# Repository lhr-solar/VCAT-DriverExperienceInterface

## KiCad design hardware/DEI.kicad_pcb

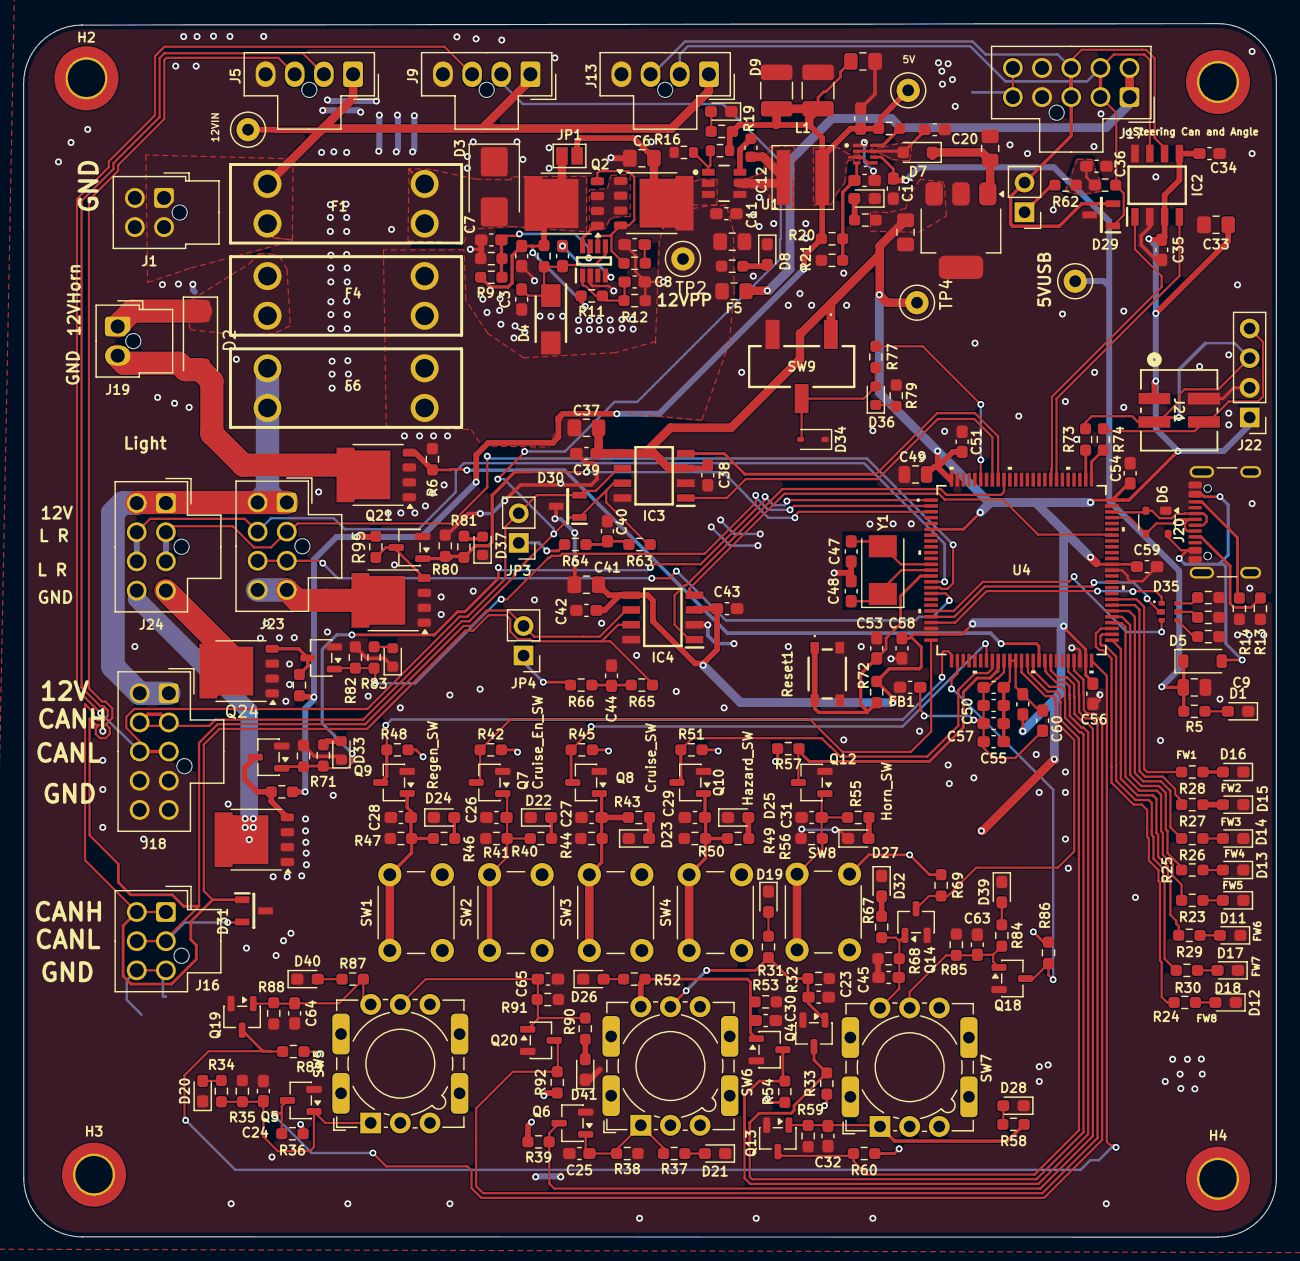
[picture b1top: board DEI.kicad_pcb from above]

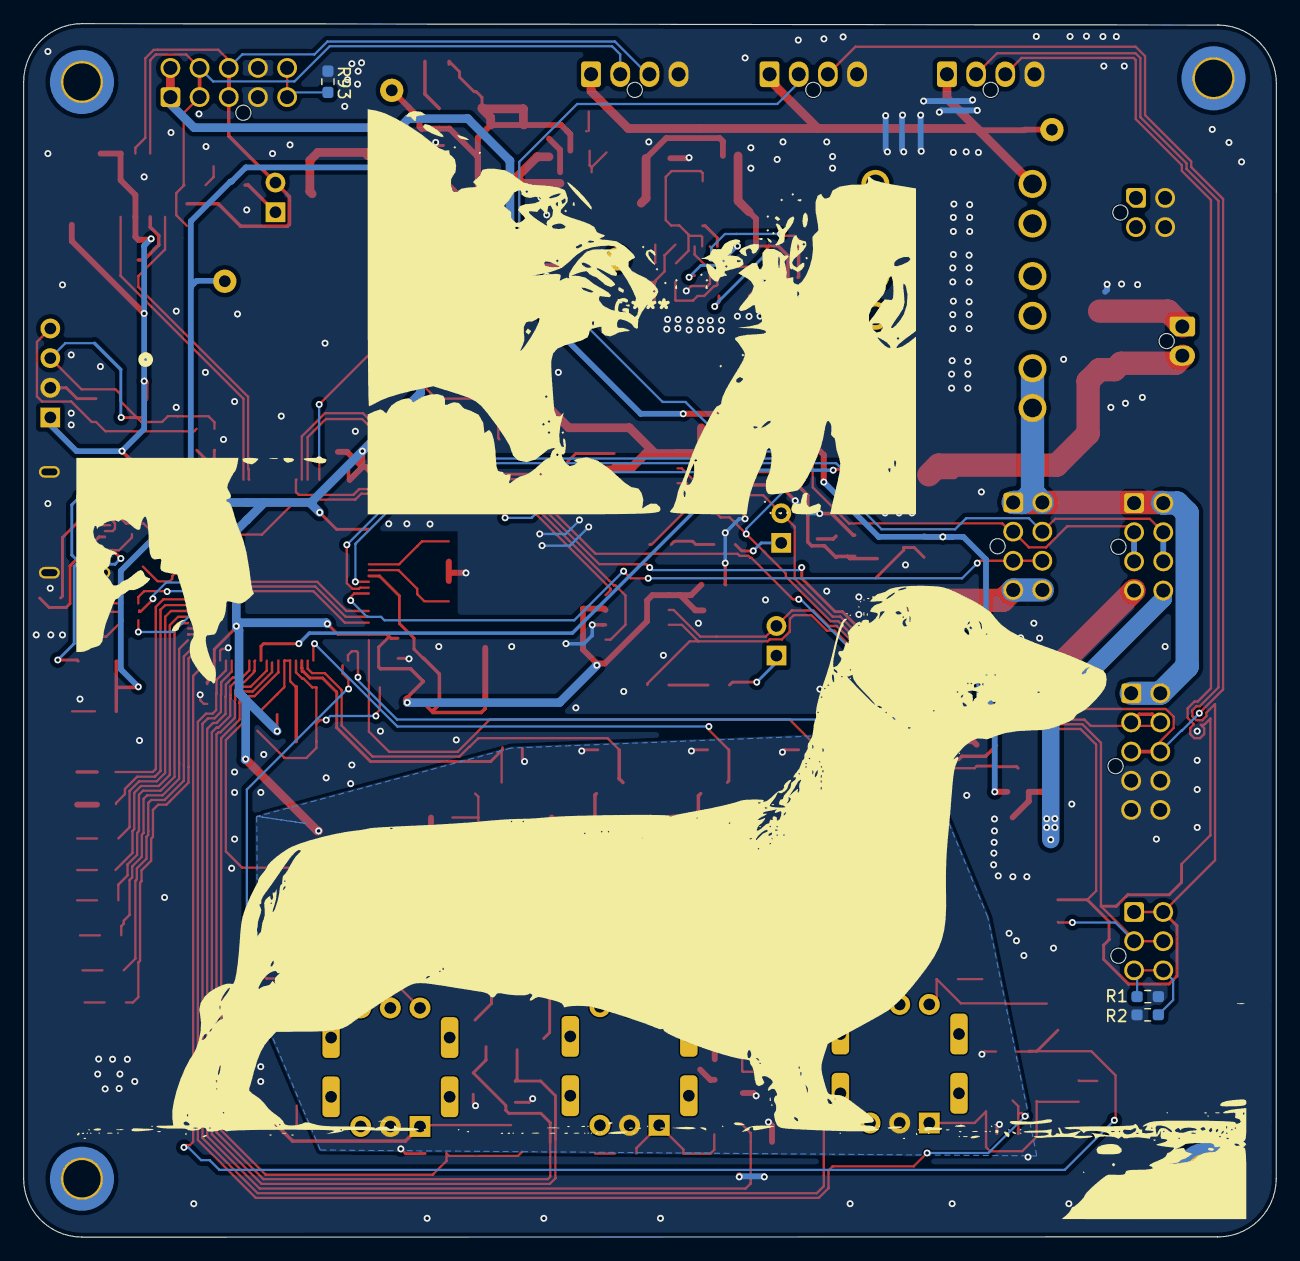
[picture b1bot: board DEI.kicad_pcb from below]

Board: 2 copper layers, 107.4 x 104.0 mm, 270 parts (3 on the bottom side), 146 nets.

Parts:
5V_USB1: TestPoint; TestPoint_Loop_D1.80mm_Drill1.0mm_Beaded
C2, C7, C8, C16, C17, C18, C19, C34, C35, C36, C38, C39, C40, C42, C43, C44, C50, C51, C52, C53, C54, C56, C58, C59, C60: 0.1u; C_0603_1608Metric_Pad1.08x0.95mm_HandSolder
C3, C55, C57: 1u; C_0603_1608Metric_Pad1.08x0.95mm_HandSolder
C4: 220n; C_0603_1608Metric_Pad1.08x0.95mm_HandSolder
C5: 10n; C_0603_1608Metric_Pad1.08x0.95mm_HandSolder
C6, C20, C21, C33, C37, C41: 10u; C_0805_2012Metric_Pad1.18x1.45mm_HandSolder
C9, C49: 10u; C_0805_2012Metric
C10: 4.7u; C_0805_2012Metric_Pad1.18x1.45mm_HandSolder
C11, C23, C24, C25, C26, C27, C28, C29, C30, C31, C32, C45, C63, C64, C65: 100n; C_0603_1608Metric_Pad1.08x0.95mm_HandSolder
C12: 100n; C_0603_1608Metric
C13, C14: 22u; C_1210_3225Metric_Pad1.33x2.70mm_HandSolder
C15: 3.3u; C_0805_2012Metric_Pad1.18x1.45mm_HandSolder
C47, C48: 26p; C_0603_1608Metric_Pad1.08x0.95mm_HandSolder
D1, D9, D10, D11, D12, D13, D14, D15, D17: Status LED; LED_0603_1608Metric_Pad1.05x0.95mm_HandSolder
D2: D; D_SlimSMA_DO-221AC_Pad1.90x1.60mm_HandSolder
D3: SMBJ15CA; D_SMB
D4: SMAF4758A; SODFL5026X125N
D5: D_Schottky; D_SOD-123
D6: SP0503BAHT; SOT-143
D7: SBA130CH-AU_R1_000A1; D_SOD-323_HandSoldering
D8: 12V Power; LED_0603_1608Metric_Pad1.05x0.95mm_HandSolder
D16: Firmware- Green LEDs; LED_0603_1608Metric_Pad1.05x0.95mm_HandSolder
D18: Firmware green led; LED_0603_1608Metric_Pad1.05x0.95mm_HandSolder
D19, D20, D21, D22, D23, D24, D25, D26, D27, D28, D32, D39, D40, D41: Blue Status; LED_0603_1608Metric_Pad1.05x0.95mm_HandSolder
D29, D30, D31: CDSOT23-T24CAN
D33, D36, D37, D38: LED; LED_0603_1608Metric
D34: TVS; D_SOD-323
D35: RGB_LED
F1: Fuse; Fuse-3557-2
F4: .5A; Fuse-3557-2
F5: 200mA; Fuse_0805_2012Metric_Pad1.15x1.40mm_HandSolder
F6: TBD; Fuse-3557-2
FB1, FB2: FerriteBead; C_0603_1608Metric_Pad1.08x0.95mm_HandSolder
H1, H2, H3, H4: m3; MountingHole_3.2mm_M3_ISO14580_Pad_TopBottom
IC1: LM74502DDFR
IC2, IC3, IC4: TCAN3413DR
J1: Power Input; Molex_Nano-Fit_105310-xx04_2x02_P2.50mm_Vertical
J5: Car_Can_Debug; Molex_Nano-Fit_105309-xx04_1x04_P2.50mm_Vertical
J9: Lighting_Can_Debug; Molex_Nano-Fit_105309-xx04_1x04_P2.50mm_Vertical
J13: Steering_Can_Debug; Molex_Nano-Fit_105309-xx04_1x04_P2.50mm_Vertical
J16: CAN_NANO_02x03; Molex_Nano-Fit_105310-xx06_2x03_P2.50mm_Vertical
J17: Steering Can; Molex_Nano-Fit_105310-xx10_2x05_P2.50mm_Vertical
J18: LightingCan; Molex_Nano-Fit_105310-xx10_2x05_P2.50mm_Vertical
J19: Horn; Molex_Nano-Fit_105309-xx02_1x02_P2.50mm_Vertical
J20: USB_C_Receptacle_USB2.0_16P; USB_C_Receptacle_GCT_USB4105-xx-A_16P_TopMnt_Horizontal
J21: SWD_Header; SWD_Conn
J22: SWD; PinHeader_1x04_P2.54mm_Vertical
J23: HeadLights; Molex_Nano-Fit_105310-xx08_2x04_P2.50mm_Vertical
J24: Light Strip; Molex_Nano-Fit_105310-xx08_2x04_P2.50mm_Vertical
JP1: SolderJumper_2_Open; SolderJumper-2_P1.3mm_Open_Pad1.0x1.5mm
JP2, JP3, JP4: TRM; PinHeader_1x02_P2.54mm_Vertical
L1: 8.2u; XAL5050822MEC
Q2, Q3, Q21, Q22, Q23, Q24: PSMN012-100YS; LFPAK56
Q4, Q5, Q6, Q7, Q8, Q9, Q10, Q11, Q12, Q13, Q14, Q15, Q16, Q17, Q18, Q19, Q20: Q_NMOS_GSD; SOT-23-3
R1, R2, R93: 0; R_0603_1608Metric_Pad0.98x0.95mm_HandSolder
R5, R19: 2.2k; R_0603_1608Metric_Pad0.98x0.95mm_HandSolder
R6, R7, R17, R33, R36, R39, R42, R45, R48, R51, R54, R57, R60, R69, R70, R72, R77, R80, R82, R86, R89, R92, R94, R95, R96: 10k; R_0603_1608Metric_Pad0.98x0.95mm_HandSolder
R8: 33; R_0603_1608Metric_Pad0.98x0.95mm_HandSolder
R9, R11, R32, R35, R38, R41, R44, R47, R50, R53, R56, R59, R68, R85, R88, R91: 100k; R_0603_1608Metric_Pad0.98x0.95mm_HandSolder
R10: 7.32k; R_0603_1608Metric_Pad0.98x0.95mm_HandSolder
R12: 15.8k; R_0603_1608Metric_Pad0.98x0.95mm_HandSolder
R13, R14, R18: 5.1k; R_0603_1608Metric_Pad0.98x0.95mm_HandSolder
R15: 100k; R_0603_1608Metric
R16: 19.1k; R_0603_1608Metric
R20: 16k; R_0603_1608Metric_Pad0.98x0.95mm_HandSolder
R21: 4.7k; R_0603_1608Metric_Pad0.98x0.95mm_HandSolder
R22, R23, R24, R25, R26, R27, R28, R29, R30, R31, R34, R37, R40, R43, R46, R49, R52, R55, R58, R67, R71, R75, R76, R78, R79, R81, R83, R84, R87, R90: 1k; R_0603_1608Metric_Pad0.98x0.95mm_HandSolder
R61, R62, R63, R64, R65, R66: 60; R_0603_1608Metric_Pad0.98x0.95mm_HandSolder
R73, R74: 22; R_0603_1608Metric_Pad0.98x0.95mm_HandSolder
Reset1: Reset; TL3365AF180QG
SW1: Regen; SW_PUSH_6mm
SW2: Cruise Enable; SW_PUSH_6mm
SW3: Cruise; SW_PUSH_6mm
SW4: Hazard; SW_PUSH_6mm
SW5, SW6, SW7: SW_SP3T_NR01103; SW_NKK_NR01
SW8: Horn; SW_PUSH_6mm
SW9: SW_SPDT; BootSW
TP1: 12V_In; TestPoint_Loop_D1.80mm_Drill1.0mm_Beaded
TP2: 12V_PP; TestPoint_Loop_D1.80mm_Drill1.0mm_Beaded
TP3: 5VBuck; TestPoint_Loop_D1.80mm_Drill1.0mm_Beaded
TP4: 3.3V_LDO; TestPoint_Loop_D1.80mm_Drill1.0mm_Beaded
U1: LMR51635XDDCR; DDC0006A-MFG
U2: TPS2117DRLR
U3: MCP1826S; SOT-223-3_TabPin2
U4: STM32G473VETx; 100PinMCU
Y1: Crystal; Crystal_SMD_Abracon_ABM3-2Pin_5.0x3.2mm

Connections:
+3.3V: C21.2, C33.1, C34.1, C35.1, C37.1, C38.1, C39.1, C41.1, C42.1, C43.1, C49.1, C51.1, C54.1, C56.1, C58.1, C59.1, FB2.1, IC2.3 (VCC), IC2.5 (SHDNV_IO), IC3.3 (VCC), IC3.5 (SHDNV_IO), IC4.3 (VCC), IC4.5 (SHDNV_IO), J21.1, J22.1, R22.1, R33.1, R36.1, R39.1, R42.1, R45.1, R48.1, R51.1, R54.1, R57.1, R60.1, R69.1, R72.2, R86.1, R89.1, R92.1, SW1.2, SW2.2, SW3.2, SW4.2, SW5.C (Common), SW6.C (Common), SW7.C (Common), SW8.2, SW9.1 (A), TP4.1 (1_1), U3.3 (VO), U4.6 (VBAT), U4.24 (VDD), U4.49 (VDD), U4.64 (VDD), U4.75 (VDD), U4.100 (VDD)
+12V: F1.1, J1.1, J1.2, J5.1 (12V), J9.1 (12V), J13.1 (12V), TP1.1 (1_1)
/5V: C13.1, C14.1, C15.1, C16.1, L1.2, R15.1, R17.1, R19.1, R20.1, R94.1, R95.1, R96.1, TP3.1 (1_1), U2.3 (VIN1), U2.5 (MODE)
/12V_Horn: D2.1 (K), F4.2, J19.1
/12V_Light: F6.2, J18.1 (12V), J18.10 (12V), J23.1, J23.8, J24.1, J24.8
/12V_Steering_Angle: F5.2, J17.1 (12V), J17.10 (12V)
/CarCan_H: D31.1 (CAN_H), IC4.7 (CANH), J5.2 (CAN_H), J16.1 (CAN_H), J16.6 (CAN_H), R65.1
/CarCan_L: D31.2 (CAN_L), IC4.6 (CANL), J5.3 (CAN_L), J16.2 (CAN_L), J16.5 (CAN_L), JP4.2 (B)
/Head: J23.3, J23.6, U4.17 (PC2)
/Head_GND: J23.4, J23.5, Q23.5
/Head_On: Q16.1 (G), R80.1, R81.1, U4.3 (PE4)
/Horn: D2.2 (A), J19.2, Q21.5
/Horn_In: Q21.4, R6.1, U4.41 (PE10)
/Left_GND: J24.5, Q22.5
/Left_On: Q15.1 (G), R70.1, R71.1, U4.1 (PE2)
/Left_Turn: J23.7, J24.6, J24.7, U4.15 (PC0)
/LightingCan_H: D30.1 (CAN_H), IC3.7 (CANH), J9.2 (CAN_H), J18.2 (CAN_H), J18.9 (CAN_H), R63.1
/LightingCan_L: D30.2 (CAN_L), IC3.6 (CANL), J9.3 (CAN_L), J18.3 (CAN_L), J18.8 (CAN_L), JP3.2 (B)
/MCU/100PinMCU/BOOT0: R77.1, U4.95 (PB8-BOOT0)
/MCU/100PinMCU/GNDA: C50.2, C52.2, C55.2, C57.2, C60.2, FB1.1, U4.35 (VSSA)
/MCU/100PinMCU/NRST: C53.1, R72.1, Reset1.1, U4.14 (PG10-NRST)
/MCU/100PinMCU/PA0: D35.5, U4.20 (PA0-GPIO_BLUE)
/MCU/100PinMCU/PA1: D35.3, U4.21 (PA1-GPIO_RED)
/MCU/100PinMCU/PA2: D35.1, U4.22 (PA2-GPIO_GREEN)
/MCU/100PinMCU/PB12: R29.2, U4.51 (PB12)
/MCU/100PinMCU/PB13: R30.2, U4.52 (PB13)
/MCU/100PinMCU/PB14: R24.2, U4.53 (PB14)
/MCU/100PinMCU/PB15: R23.2, U4.54 (PB15)
/MCU/100PinMCU/PD8: R25.2, U4.55 (PD8)
/MCU/100PinMCU/PD9: R26.2, U4.56 (PD9)
/MCU/100PinMCU/PD10: R27.2, U4.57 (PD10)
/MCU/100PinMCU/PD11: R28.2, U4.58 (PD11)
/MCU/100PinMCU/SWCLK: R73.1, U4.77 (PA14)
/MCU/100PinMCU/SWDIO: R74.1, U4.76 (PA13)
/MCU/100PinMCU/VDDA: C50.1, C52.1, C55.1, C57.1, C60.1, FB2.2, U4.36 (VREF+), U4.37 (VDDA)
/MCU/CARCAN_RX: IC4.4 (RXD), U4.69 (PA8)
/MCU/CARCAN_TX: IC4.1 (TXD), U4.91 (PB4)
/MCU/Cruise_Out: Q8.3 (D), R45.2, U4.32 (PB0)
/MCU/Cruise_enable_out: Q7.3 (D), R42.2, U4.25 (PA3)
/MCU/GEAR_F_IN: C32.1, Q13.1 (G), R58.1, R59.1, SW7.1
/MCU/Gear_F_Out: Q13.3 (D), R60.2, U4.39 (PE8)
/MCU/Gear_N: C45.1, Q14.1 (G), R67.1, R68.1, SW7.2
/MCU/Gear_N_Out: Q14.3 (D), R69.2, U4.38 (PE7)
/MCU/Gear_out: Q18.3 (D), R86.2, U4.27 (PA5)
/MCU/Hazard_Out: Q10.3 (D), R51.2, U4.33 (PB1)
/MCU/Horn_Out: Q12.3 (D), R57.2, U4.34 (PB2)
/MCU/IGN_ARR_IN: C30.1, Q11.1 (G), R52.1, R53.1, SW6.2
/MCU/IGN_ARR_O: Q11.3 (D), R54.2, U4.42 (PE11)
/MCU/IGN_MTR_IN: C25.1, Q6.1 (G), R37.1, R38.1, SW6.1
/MCU/IGN_O: Q6.3 (D), R39.2, U4.43 (PE12)
/MCU/IGN_O_Out: Q4.3 (D), R33.2, U4.40 (PE9)
/MCU/IGN_Off: C23.1, Q4.1 (G), R31.1, R32.1, SW6.3
/MCU/LIGHTCAN_RX: IC3.4 (RXD), U4.92 (PB5)
/MCU/LIGHTCAN_TX: IC3.1 (TXD), U4.93 (PB6)
/MCU/NMOS4/Gate: C26.1, Q7.1 (G), R40.1, R41.1, SW2.1
/MCU/NMOS5/Gate: C27.1, Q8.1 (G), R43.1, R44.1, SW3.1
/MCU/NMOS6/Gate: C28.1, Q9.1 (G), R46.1, R47.1, SW1.1
/MCU/NMOS7/Gate: C29.1, Q10.1 (G), R49.1, R50.1, SW4.1
/MCU/NMOS11/Gate: C31.1, Q12.1 (G), R55.1, R56.1, SW8.1
/MCU/NMOS16/Gate: C63.1, Q18.1 (G), R84.1, R85.1, SW7.3
/MCU/Regen_Out: Q9.3 (D), R48.2, U4.26 (PA4)
/MCU/STEERCAN_RX: IC2.4 (RXD), U4.82 (PD0)
/MCU/STEERCAN_TX: IC2.1 (TXD), U4.83 (PD1)
/MCU/Steering_M: C64.1, Q19.1 (G), R87.1, R88.1, SW5.2
/MCU/Turn_L_IN: C24.1, Q5.1 (G), R34.1, R35.1, SW5.1
/MCU/Turn_L_Out: Q5.3 (D), R36.2, U4.47 (PB10)
/MCU/Turn_Middle: Q19.3 (D), R89.2, U4.50 (PB11)
/MCU/Turn_R_IN: C65.1, Q20.1 (G), R90.1, R91.1, SW5.3
/MCU/Turn_R_out: Q20.3 (D), R92.2, U4.46 (PE15)
/Power/12VBuck/CB: C12.1, U1.6 (CB)
/Power/12VBuck/FB: R15.2, R16.1, U1.1 (FB)
/Power/12VBuck/SW: C12.2, L1.1, U1.5 (SW)
/Power/12VBuck/V_in_12V: C6.1, C10.1, C11.1, F4.1, F5.1, F6.1, JP1.2 (B), Q3.5, R18.1, TP2.1 (1_1), U1.2 (EN), U1.3 (VIN)
/Power/LDO/Vin: C19.1, D7.2 (A), U2.2 (VOUT), U2.7 (VOUT__1)
/Power/PowerProtection/EN/UVLO: C8.1, IC1.1 (EN/UVLO), R11.2, R12.2
/Power/PowerProtection/OV: C7.1, IC1.7 (OV), R9.2, R10.1
/Power/PowerProtection/Vin: C2.1, D3.2 (A2), F1.2, JP1.1 (A), Q2.5, R7.2, R9.1, R11.1
/Power/PowerProtection/gate: IC1.6 (GATE), Q2.4, Q3.4, R8.2
/Power/PowerProtection/source: IC1.8 (SRC), Q2.1, Q2.2, Q2.3, Q3.1, Q3.2, Q3.3
/Power/Power_Mux/PR1: C18.1, R20.2, R21.1, U2.4 (PR1)
/Right_GND: J24.4, Q24.5
/Right_On: Q17.1 (G), R82.1, R83.1, U4.2 (PE3)
/Right_Turn: J23.2, J24.2, J24.3, U4.16 (PC1)
/SteeringCan_H: D29.1 (CAN_H), IC2.7 (CANH), J13.2 (CAN_H), J17.2 (CAN_H), J17.9 (CAN_H), R61.1
/SteeringCan_L: D29.2 (CAN_L), IC2.6 (CANL), J13.3 (CAN_L), J17.3 (CAN_L), J17.8 (CAN_L), JP2.2 (B)
/USB5V: 5V_USB1.1 (1_1), C9.2, C17.1, D5.1 (K), R5.1, U2.6 (VIN2)
/USB-C_Connector/CC1: J20.A5 (CC1), R13.2
/USB-C_Connector/CC2: J20.B5 (CC2), R14.2
/USB-C_Connector/VBUS_IN: D5.2 (A), D6.4 (K), J20.A4 (VBUS), J20.A9 (VBUS), J20.B4 (VBUS), J20.B9 (VBUS)
/USB_D+: D6.2 (K), J20.A6 (D+), J20.B6 (D+), U4.73 (PA12)
/USB_D-: D6.3 (K), J20.A7 (D-), J20.B7 (D-), U4.72 (PA11)
GND: C2.2, C3.1, C5.2, C6.2, C7.2, C8.2, C9.1, C10.2, C11.2, C13.2, C14.2, C15.2, C16.2, C17.2, C18.2, C19.2, C20.1, C21.1, C23.2, C24.2, C25.2, C26.2, C27.2, C28.2, C29.2, C30.2, C31.2, C32.2, C33.2, C34.2, C35.2, C36.1, C37.2, C38.2, C39.2, C40.1, C41.2, C42.2, C43.2, C44.1, C45.2, C47.1, C48.1, C49.2, C51.2, C53.2, C54.2, C56.2, C58.2, C59.2, C63.2, C64.2, C65.2, D1.1 (K), D3.1 (A1), D4.2 (A), D6.1 (A), D8.1 (K), D9.1 (K), D10.1 (K), D11.1 (K), D12.1 (K), D13.1 (K), D14.1 (K), D15.1 (K), D16.1 (K), D17.1 (K), D18.1 (K), D19.1 (K), D20.1 (K), D21.1 (K), D22.1 (K), D23.1 (K), D24.1 (K), D25.1 (K), D26.1 (K), D27.1 (K), D28.1 (K), D29.3 (GND), D30.3 (GND), D31.3 (GND), D32.1 (K), D33.1 (K), D34.1 (A1), D37.1 (K), D38.1 (K), D39.1 (K), D40.1 (K), D41.1 (K), FB1.2, IC1.2 (GND), IC2.2 (GND), IC2.8 (STB), IC3.2 (GND), IC3.8 (STB), IC4.2 (GND), IC4.8 (STB), J1.3, J1.4, J5.4 (GND), J9.4 (GND), J13.4 (GND), J17.4 (GND), J17.7 (GND), J18.4 (GND), J18.5 (SHIELD), J18.6 (SHIELD), J18.7 (GND), J20.A1 (GND), J20.A12 (GND), J20.B1 (GND), J20.B12 (GND), J20.S1 (SHIELD), J20.S2 (Shield), J20.S3 (Shield), J20.S4 (Shield), J21.2, J22.2, Q4.2 (S), Q5.2 (S), Q6.2 (S), Q7.2 (S), Q8.2 (S), Q9.2 (S), Q10.2 (S), Q11.2 (S), Q12.2 (S), Q13.2 (S), Q14.2 (S), Q15.2 (S), Q16.2 (S), Q17.2 (S), Q18.2 (S), Q19.2 (S), Q20.2 (S), Q21.1, Q21.2, Q21.3, Q22.1, Q22.2, Q22.3, Q23.1, Q23.2, Q23.3, Q24.1, Q24.2, Q24.3, R1.2, R2.2, R6.2, R10.2, R12.1, R13.1, R14.1, R16.2, R21.2, R32.2, R35.2, R38.2, R41.2, R44.2, R47.2, R50.2, R53.2, R56.2, R59.2, R68.2, R70.2, R75.2, R76.2, R78.2, R79.2, R80.2, R82.2, R85.2, R88.2, R91.2, R93.2, Reset1.2, SW9.3 (C), U1.4 (GND), U2.1 (GND), U3.2 (GND), U4.23 (VSS), U4.48 (VSS), U4.63 (VSS), U4.74 (VSS), U4.99 (VSS)
unnamed: C5.1, R8.1
unnamed: C36.2, R61.2, R62.1
unnamed: C40.2, R63.2, R64.1
unnamed: C44.2, R65.2, R66.1
unnamed: D1.2 (A), R5.2
unnamed: C3.2, C4.1, D4.1 (K), IC1.5 (VS), R7.1
unnamed: C20.2, D7.1 (K), U3.1 (VI)
unnamed: D8.2 (A), R18.2
unnamed: D9.2 (A), R19.2
unnamed: D10.2 (A), R22.2
unnamed: D11.2 (A), R23.1
unnamed: D12.2 (A), R24.1
unnamed: D13.2 (A), R25.1
unnamed: D14.2 (A), R26.1
unnamed: D15.2 (A), R27.1
unnamed: D16.2 (A), R28.1
unnamed: D17.2 (A), R29.1
unnamed: D18.2 (A), R30.1
unnamed: D19.2 (A), R31.2
unnamed: D20.2 (A), R34.2
unnamed: D21.2 (A), R37.2
unnamed: D22.2 (A), R40.2
unnamed: D23.2 (A), R43.2
unnamed: D24.2 (A), R46.2
unnamed: D25.2 (A), R49.2
unnamed: D26.2 (A), R52.2
unnamed: D27.2 (A), R55.2
unnamed: D28.2 (A), R58.2
unnamed: D32.2 (A), R67.2
unnamed: D33.2 (A), R71.2
unnamed: D34.2 (A2), D36.2 (A), R77.2, SW9.2 (B)
unnamed: D35.2, R75.1
unnamed: D35.4, R76.1
unnamed: D35.6, R78.1
unnamed: D36.1 (K), R79.1
unnamed: D37.2 (A), R81.2
unnamed: D38.2 (A), R83.2
unnamed: D39.2 (A), R84.2
unnamed: D40.2 (A), R87.2
unnamed: D41.2 (A), R90.2
unnamed: C4.2, IC1.4 (VCAP)
unnamed: J16.3 (SHIELD), J16.4 (SHIELD), R1.1, R2.1
unnamed: J17.5 (SHIELD), J17.6 (SHIELD), R93.1
unnamed: J21.3, J22.3, R73.2
unnamed: J21.4, J22.4, R74.2
unnamed: JP2.1 (A), R62.2
unnamed: JP3.1 (A), R64.2
unnamed: JP4.1 (A), R66.2
unnamed: Q15.3 (D), Q22.4, R94.2
unnamed: Q16.3 (D), Q23.4, R95.2
unnamed: Q17.3 (D), Q24.4, R96.2
unnamed: R17.2, U2.8 (ST)
unnamed: C47.2, U4.12 (PF0-OSC_IN), Y1.2
unnamed: C48.2, U4.13 (PF1-OSC_OUT), Y1.1
